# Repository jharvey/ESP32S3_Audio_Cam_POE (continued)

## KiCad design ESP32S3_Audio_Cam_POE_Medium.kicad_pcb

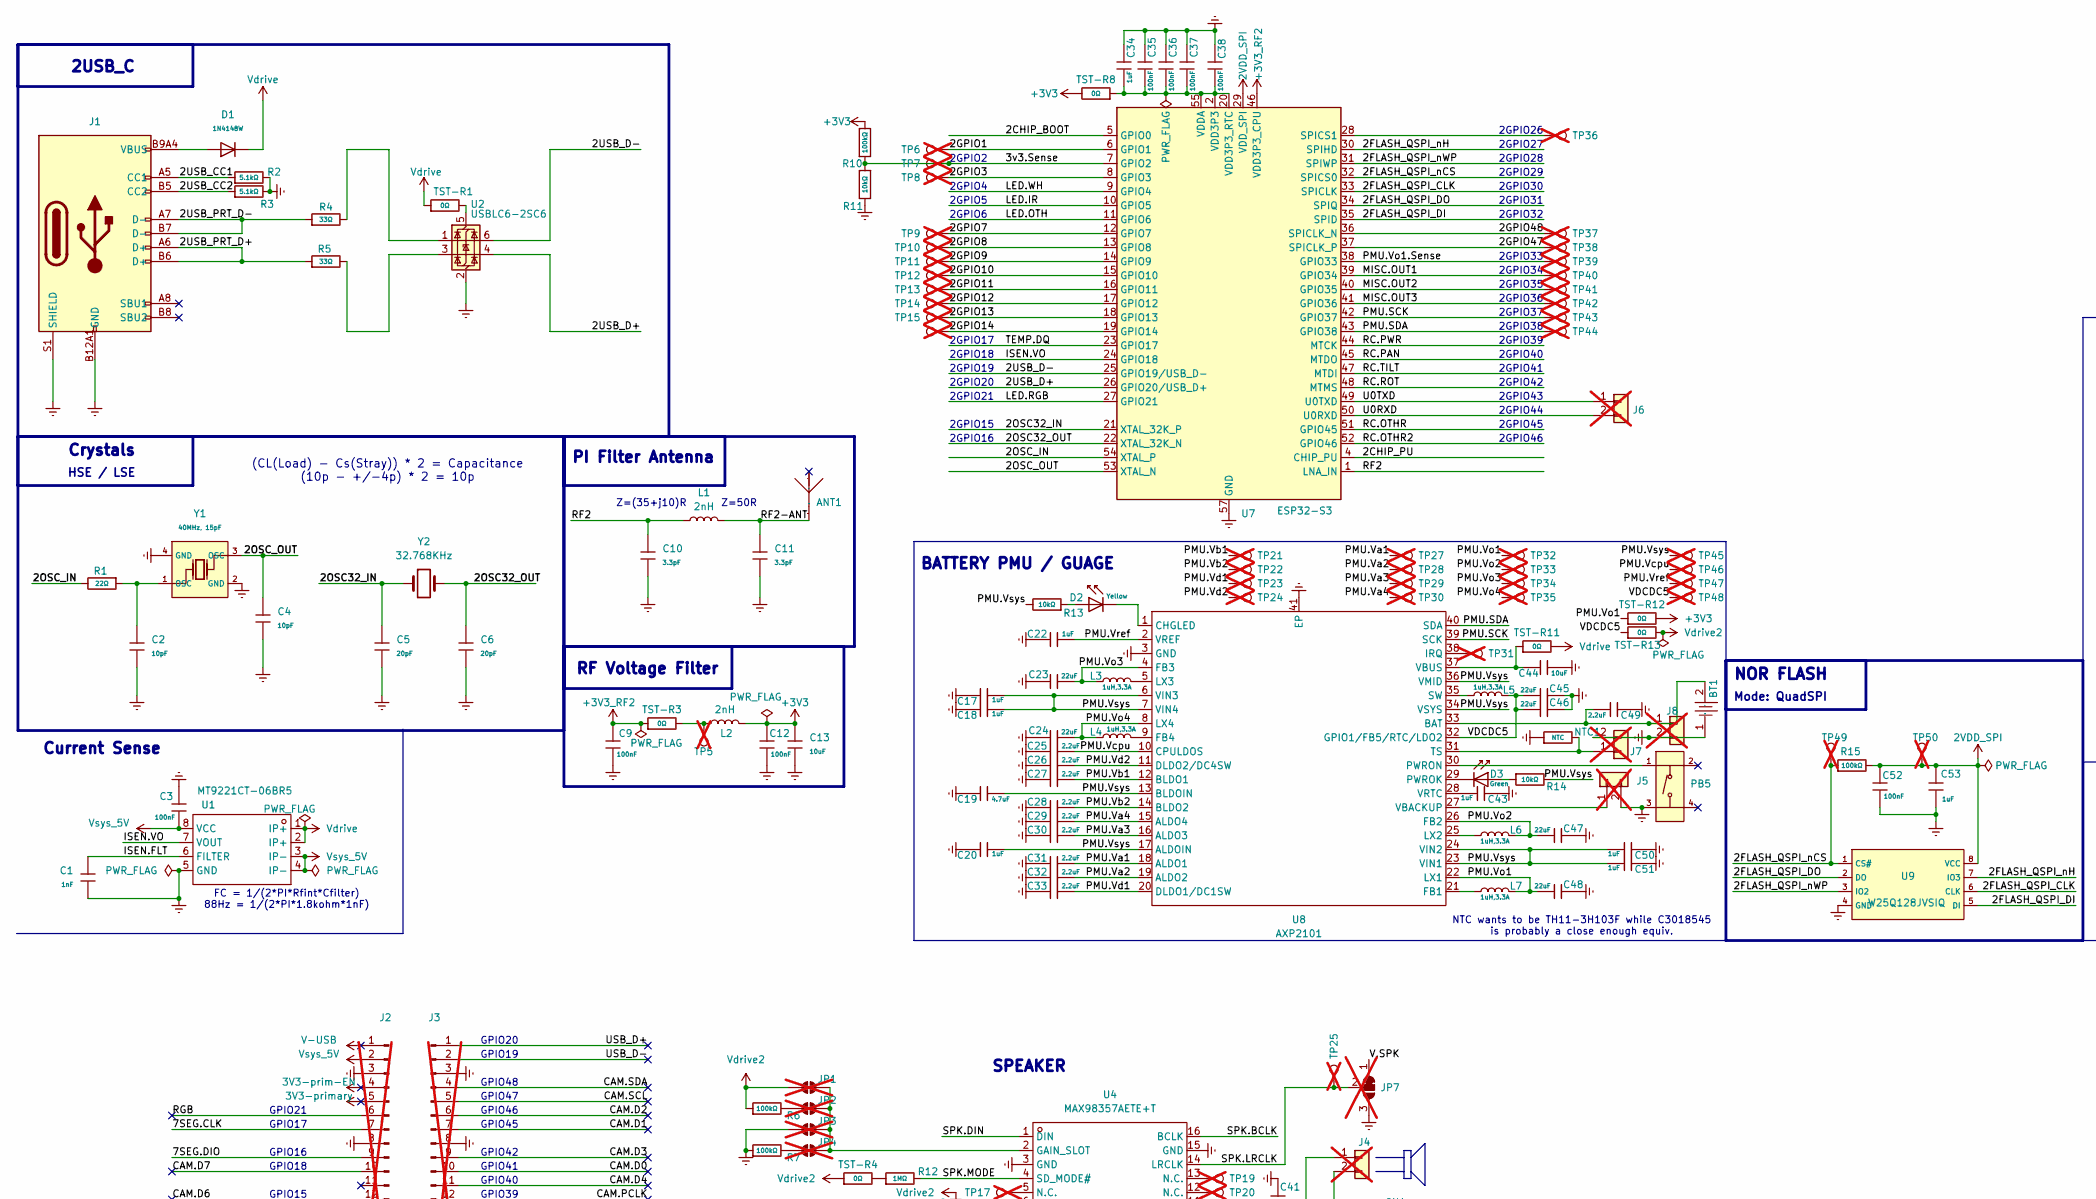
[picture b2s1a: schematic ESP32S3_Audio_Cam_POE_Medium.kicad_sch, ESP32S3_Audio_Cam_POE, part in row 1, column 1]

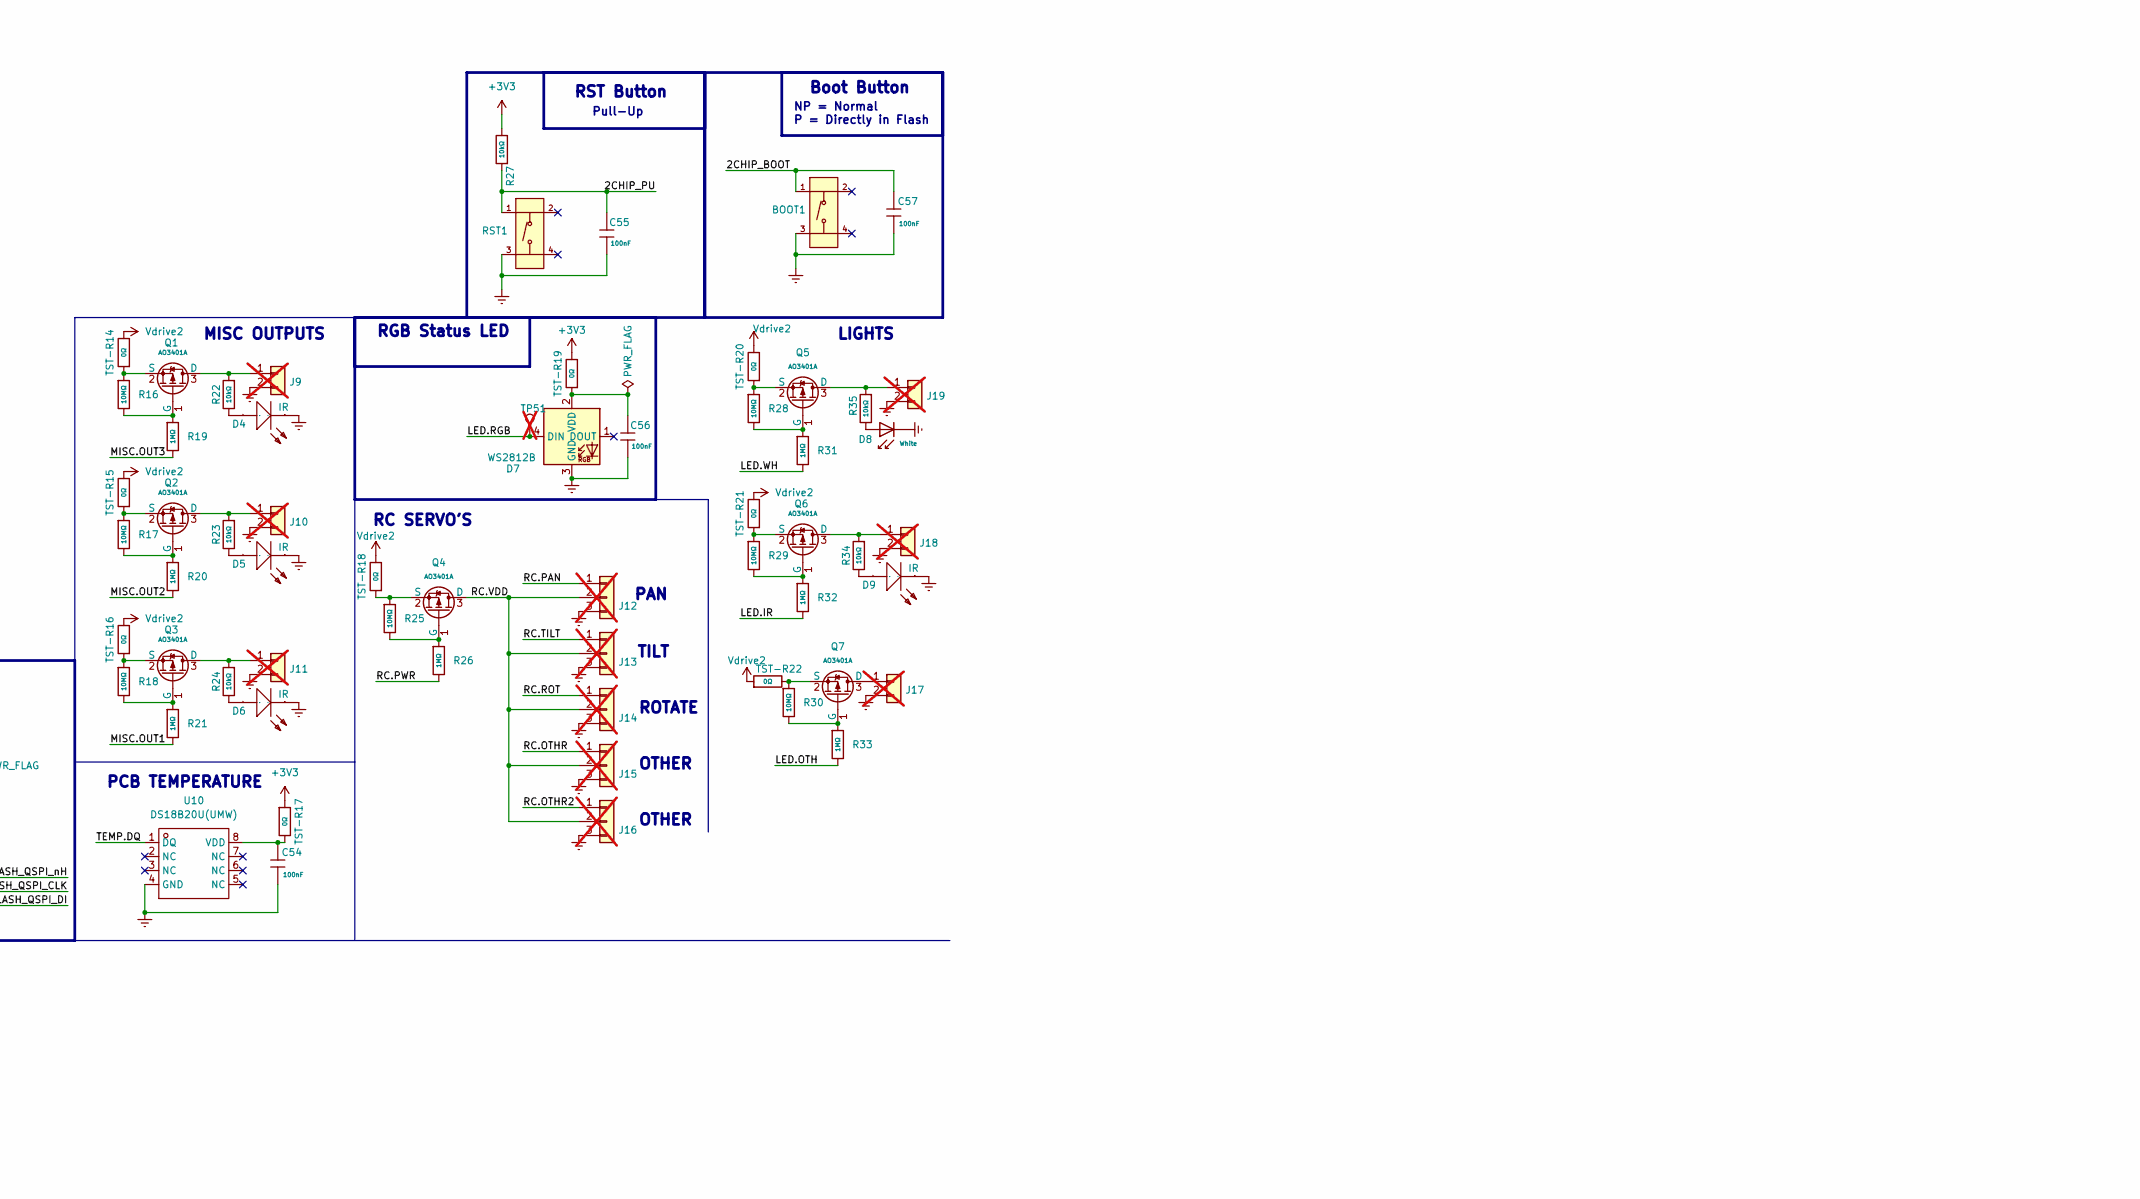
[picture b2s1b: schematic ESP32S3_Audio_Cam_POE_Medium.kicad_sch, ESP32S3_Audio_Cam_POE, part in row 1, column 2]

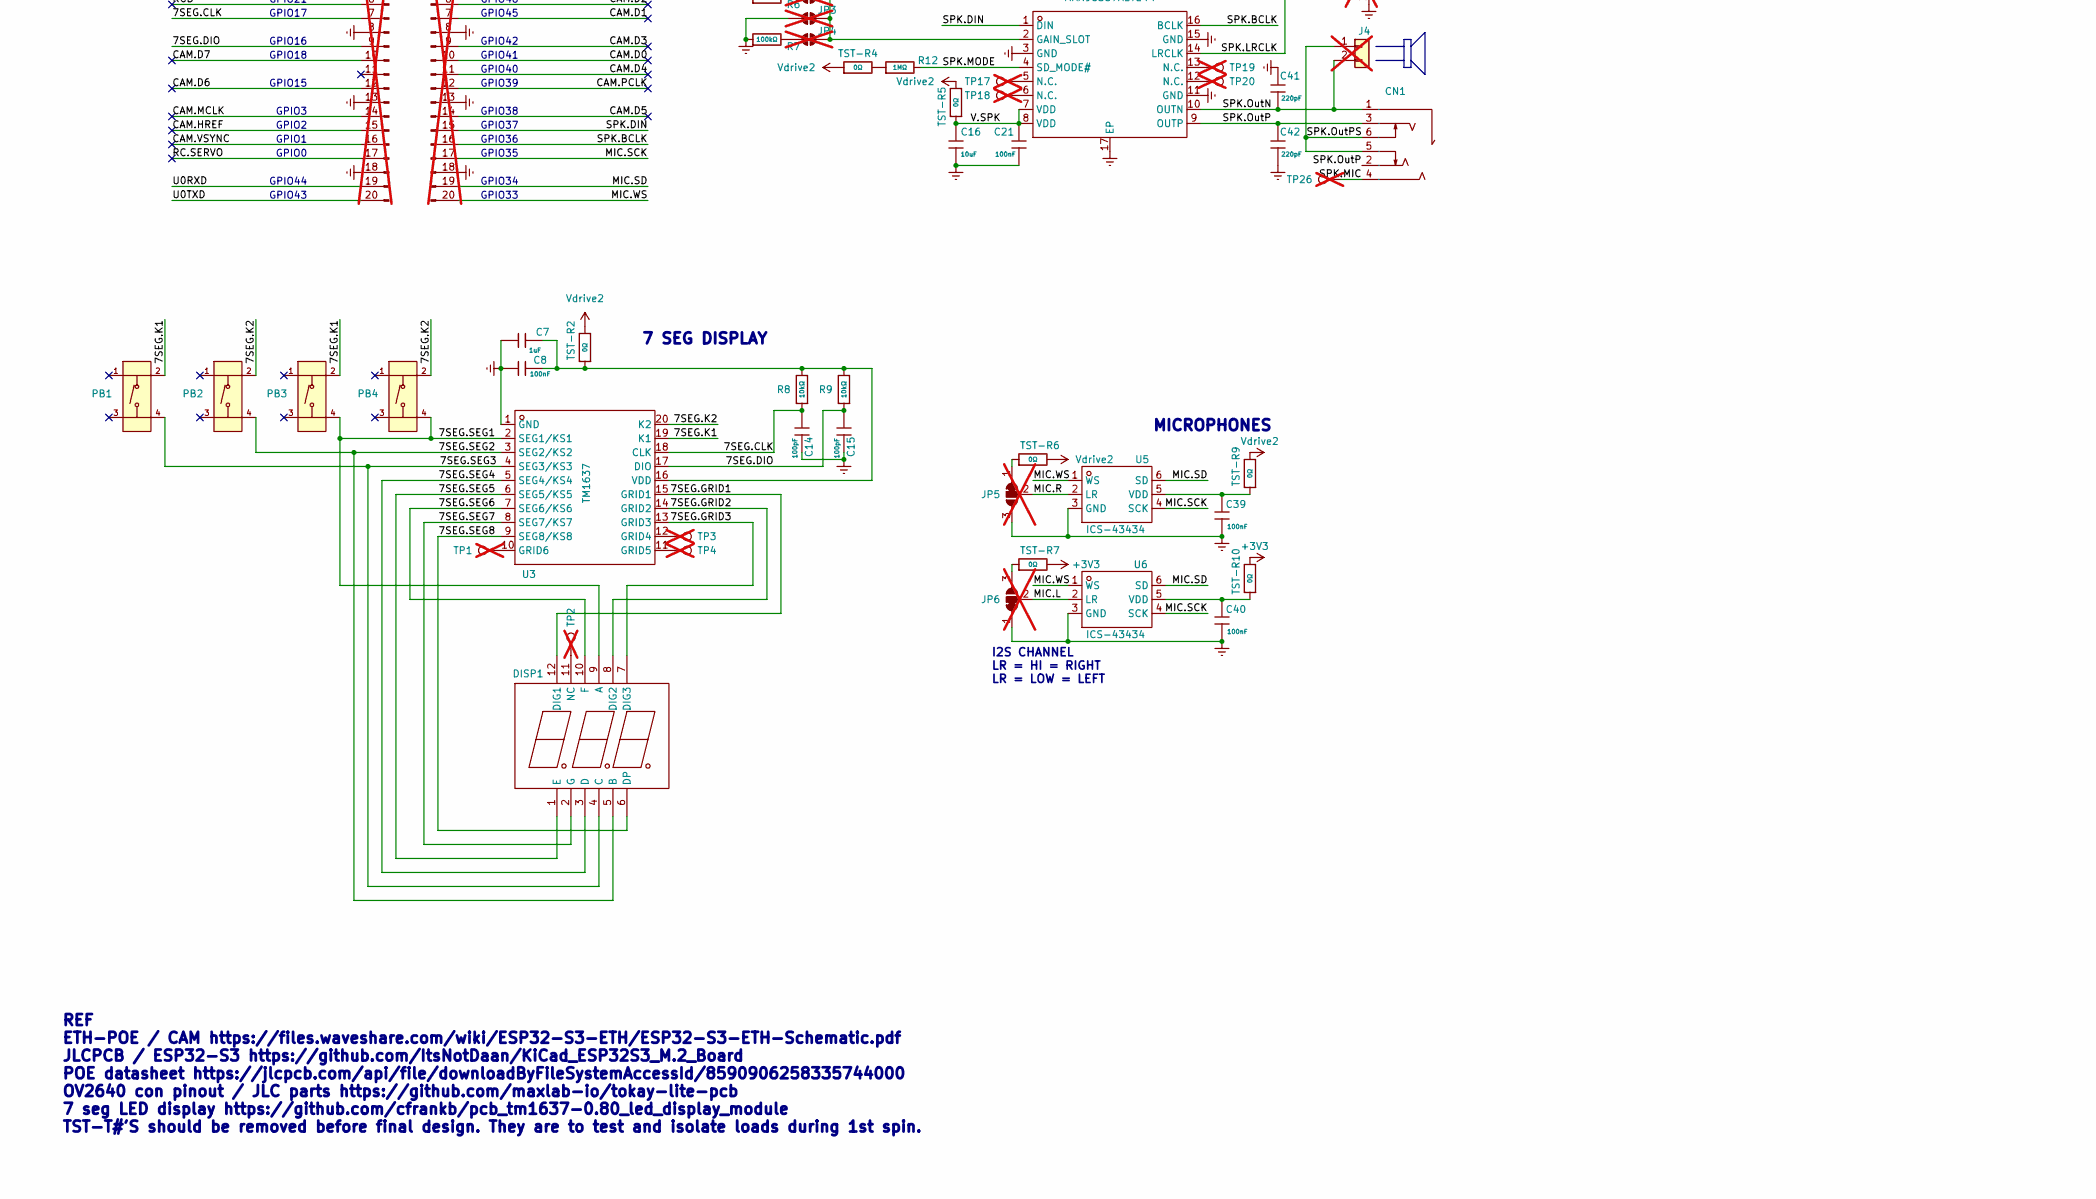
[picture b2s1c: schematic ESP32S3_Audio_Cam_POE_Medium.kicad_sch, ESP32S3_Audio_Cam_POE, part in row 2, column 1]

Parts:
ANT1: KH-3216-H0209; ANT-SMD_L3.2-W1.6-KH-3216F245C04; Manufacturer_Part_Number KH-3216-H0209; LCSC PART # C2925417
BOOT1: Tactile Button, 160gf; SW-SMD_4P-L5.1-W5.1-P3.70-LS6.5-TL-2; Voltage Rating (Dc) 12V; Part TS-1187A-B-A-B; LCSC C318884
BT1: BH-18650-B1BA002; BATTERY-SMD_18650-1S-L77.1-W20.7-1; Manufacturer Part BH-18650-B1BA002; LCSC C2988620
C1: 1nF; C_0402; Voltage Rated 50V; Tolerance ±10%; Part 0402B102K500NT; LCSC C1523
C2, C4: 10pF; C_0402; Voltage Rated 50V; Tolerance ±5%; Part CL05C100JB5NNNC; LCSC C32949
C3, C8, C9, C12, C21, C35, C36, C37, C38, C39, C40, C52, C54, C55, C56, C57: 100nF; C_0603; Voltage Rated 50V; Tolerance ±10%; Part CC0603KRX7R9BB104; LCSC C14663
C5, C6: 20pF; C_0402; Voltage Rated 50V; Tolerance ±5%; Part 0402CG200J500NT; LCSC C1554
C7, C34, C53: 1uF; C_0603; Voltage Rated 50V; Tolerance ±10%; Part CL10A105KB8NNNC; LCSC C15849
C10, C11: 3.3pF; C_0402; Voltage Rated 50V; Part 0402CG3R3C500NT; LCSC C1565
C13, C44: 10uF; C_0402; Voltage Rated 6.3V; Tolerance ±20%; Part CL05A106MQ5NUNC; LCSC C15525
C14, C15: 100pF; C_0402; Voltage Rated 50V; Tolerance ±5%; Part 0402CG101J500NT; LCSC C1546
C16: 10uF; C_0805; Voltage Rated 50V; Tolerance ±10%; Part GRM21BR61H106KE43L; LCSC C440198
C17, C18, C20, C22, C43, C50, C51: 1uF; C_0402; Voltage Rated 25V; Tolerance ±10%; Part CL05A105KA5NQNC; LCSC C52923
C19: 4.7uF; C_0402; Voltage Rated 10V; Tolerance ±20%; Part CL05A475MP5NRNC; LCSC C23733
C23, C24, C45, C46, C47, C48: 22uF; C_0603; Voltage Rated 6.3V; Tolerance ±20%; Part CL10A226MQ8NRNC; LCSC C59461
C25, C26, C27, C28, C29, C30, C31, C32, C33, C49: 2.2uF; C_0402; Voltage Rated 6.3V; Tolerance ±20%; Part CL05A225MQ5NSNC; LCSC C12530
C41, C42: 220pF; C_0402; Voltage Rated 50V; Tolerance ±10%; Part 0402B221K500NT; LCSC C1530
CN1: PJ-316C-6A; SMD_3.5mm_Audio_Connectors_(Headphones)_C707223; Manufacturer Part PJ-316C-6A; LCSC C707223
D1: 1N4148W; D_SOD-123; Forward Voltage (Vf@If) 1V@50mA; Reverse Voltage (Vr) 75V; Part 1N4148W; LCSC C81598
D2: Yellow; D_0805; Part KT-0805Y; LCSC C2296
D3: Green; D_0805; Part KT-0805G; LCSC C2297
D4, D5, D6, D9: IR; IR-LED_C131280; LCSC C131280
D7: WS2812B; LED-SMD_4P-L1.6-W1.5_XL-1615RGBC-WS2812B; LCSC C5349954
D8: White; D_0603; Part KT-0603W; LCSC C2290
DISP1: SLS0563DRA1GD; 3x7-seg_LED-RED_C2913084; LCSC C2913084
J1: Connector, USB-TYPE-C-16P; TYPE-C-SMD_HX-TYPE-C-16PIN; LCSC C2927039
J2, J3: Conn_01x20_Pin; PinHeader_1x20_P2.54mm_Vertical; not fitted
J4, J5, J6, J7, J8, J9, J10, J11, J17, J18, J19: Conn_01x02; PinHeader_1x02_P1.00mm_Vertical; not fitted
J12, J13, J14, J15, J16: Conn_01x03; PinHeader_1x03_P2.54mm_Vertical; not fitted
JP1, JP2, JP3, JP4: SolderJumper_2_Open; SolderJumper-2_P1.3mm_Open_TrianglePad1.0x1.5mm; not fitted
JP5, JP6, JP7: SolderJumper_3_Bridged12; SolderJumper-3_P1.3mm_Bridged12_Pad1.0x1.5mm; not fitted
L1, L2: 2nH; L_0603_1608Metric_Pad1.05x0.95mm_HandSolder; LCSC PART # C29682
L3, L4, L5, L6, L7: 1uH,3.3A; L_1008_2520Metric; Tolerance ±10%; Part SDFL2012Q1R0KTF; LCSC C435392
NTC1: NTC; R_0402; Overload Voltage (Max) 50V; Tolerance ±1%; Part 0402WGF1002TCE; LCSC C3018545
PB1, PB2, PB3, PB4, PB5: Tactile Button, 160gf; SW-SMD_4P-L5.1-W5.1-P3.70-LS6.5-TL-2; Voltage Rating (Dc) 12V; Part TS-1187A-B-A-B; LCSC C318884
Q1, Q2, Q3, Q4, Q5, Q6, Q7: AO3401A; Q_SOT-23; Part AO3401A; LCSC C15127
R1: 22Ω; R_0402; Overload Voltage (Max) 50V; Tolerance ±1%; Part 0402WGF220JTCE; LCSC C25092
R2, R3: 5.1kΩ; R_0402; Overload Voltage (Max) 50V; Tolerance ±1%; Part 0402WGF5101TCE; LCSC C25905
R4, R5: 33Ω; R_0402; Overload Voltage (Max) 50V; Tolerance ±1%; Part 0402WGF330JTCE; LCSC C25105
R6, R7: 100kΩ; R_0805; Overload Voltage (Max) 150V; Tolerance ±1%; Part 0805W8F1003T5E; LCSC C149504
R8, R9, R11, R13, R14, R22, R23, R24, R27, R34, R35: 10kΩ; R_0402; Overload Voltage (Max) 50V; Tolerance ±1%; Part 0402WGF1002TCE; LCSC C25744
R10, R15: 100kΩ; R_0402; Overload Voltage (Max) 50V; Tolerance ±1%; Part 0402WGF1003TCE; LCSC C25741
R12, R19, R20, R21, R26, R31, R32, R33: 1MΩ; R_0402; Overload Voltage (Max) 50V; Tolerance ±1%; Part 0402WGF1004TCE; LCSC C26083
R16, R17, R18, R25, R28, R29, R30: 10MΩ; R_0402; Overload Voltage (Max) 50V; Tolerance ±1%; Part 0402WGF1005TCE; LCSC C26082
RST1: Tactile Button, 160gf; SW-SMD_4P-L5.1-W5.1-P3.70-LS6.5-TL-2; Voltage Rating (Dc) 12V; Part TS-1187A-B-A-B; LCSC C318884
TP1, TP2, TP3, TP4, TP5, TP6, TP7, TP8, TP9, TP10, TP11, TP12, TP13, TP14, TP15, TP16, TP17, TP18, TP19, TP20, TP26, TP31, TP36, TP37, TP38, TP39, TP40, TP41, TP42, TP43, TP44, TP49, TP50, TP51: TestPoint; TestPoint_Pad_D1.0mm; not fitted
TP21, TP22, TP23, TP24, TP25, TP27, TP28, TP29, TP30, TP32, TP33, TP34, TP35, TP45, TP46, TP47, TP48: TestPoint; PinHeader_1x01_P1.00mm_Vertical; not fitted
TST-R1, TST-R2, TST-R3, TST-R4, TST-R5, TST-R6, TST-R7, TST-R8, TST-R9, TST-R10, TST-R11, TST-R12, TST-R13, TST-R14, TST-R15, TST-R16, TST-R17, TST-R18, TST-R19, TST-R20, TST-R21, TST-R22: 0Ω; R_0603; Overload Voltage (Max) 75V; Tolerance ±1%; Part 0603WAF0000T5E; LCSC C21189
U1: MT9221CT-06BR5; Current-sensor_MT9221CT-06BR5_C879632; LCSC C879632
U2: USBLC6-2SC6; SOT-23-6; Manufacturer_Part_Number USBLC6-2SC6; LCSC PART # C2827654
U3: TM1637; digital tube drivers_c2962580; LCSC C2962580
U4: MAX98357AETE+T; MAX98357AETE+T_C910544; Manufacturer Part MAX98357AETE+T
U5, U6: ICS-43434; ICS-43434_C5656610; LCSC C5656610
U7: ESP32-S3; QFN-56-1EP_7x7mm_P0.4mm_EP4x4mm_ThermalVias; LCSC C2913194
U8: AXP2101; QFN-40-1EP_5x5mm_P0.4mm_EP3.6x3.6mm_ThermalVias; LCSC C3036461
U9: W25Q128JVSIQ; SOIC-8_L5.3-W5.3-P1.27-LS8.0-BL; Part W25Q128JVSIQ; LCSC PART # C97521
U10: DS18B20U(UMW); DS18B20_C695836; LCSC C695836
Y1: 40MHz, 15pF; OSC-SMD_4P-L3.2-W2.5-BL_SIT8008BI; PartID X322540MPB4SI; LCSC C9010
Y2: 32.768KHz; Crystal_SMD_3215-2Pin_3.2x1.5mm; Manufacturer_Part_Number DST310S 32.768KHz; LCSC PART # C97604

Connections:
2VDD_SPI: C52.2, C53.1, R15.2, TP50.1, U7.29 (VDD_SPI), U9.8 (VCC)
3V3-prim-EN: J2.4
3V3-primary: J2.5
+3V3: C12.2, C13.1, L2.2, R10.2, R27.2, TST-R7.2, TST-R8.2, TST-R10.2, TST-R12.2, TST-R17.1, TST-R19.2
+3V3_RF2: C9.2, TST-R3.1, U7.46 (VDD3P3_CPU)
/2CHIP_BOOT: BOOT1.1 (A), C57.2, U7.5 (GPIO0)
/2CHIP_PU: C55.2, R27.1, RST1.1 (A), U7.4 (CHIP_PU)
/2FLASH_QSPI_CLK: U7.33 (SPICLK), U9.6 (CLK)
/2FLASH_QSPI_DI: U7.35 (SPID), U9.5 (DI)
/2FLASH_QSPI_DO: U7.34 (SPIQ), U9.2 (DO)
/2FLASH_QSPI_nCS: R15.1, TP49.1, U7.32 (SPICS0), U9.1 (CS#)
/2FLASH_QSPI_nH: U7.30 (SPIHD), U9.7 (IO3)
/2FLASH_QSPI_nWP: U7.31 (SPIWP), U9.3 (IO2)
/2GPIO1: TP6.1, U7.6 (GPIO1)
/2GPIO3: TP8.1, U7.8 (GPIO3)
/2GPIO7: TP9.1, U7.12 (GPIO7)
/2GPIO8: TP10.1, U7.13 (GPIO8)
/2GPIO9: TP11.1, U7.14 (GPIO9)
/2GPIO10: TP12.1, U7.15 (GPIO10)
/2GPIO11: TP13.1, U7.16 (GPIO11)
/2GPIO12: TP14.1, U7.17 (GPIO12)
/2GPIO13: TP15.1, U7.18 (GPIO13)
/2GPIO14: TP16.1, U7.19 (GPIO14)
/2GPIO47: TP38.1, U7.37 (SPICLK_P)
/2GPIO48: TP37.1, U7.36 (SPICLK_N)
/2OSC32_IN: C5.1, U7.21 (XTAL_32K_P), Y2.1
/2OSC32_OUT: C6.1, U7.22 (XTAL_32K_N), Y2.2
/2OSC_IN: R1.2, U7.54 (XTAL_P)
/2OSC_OUT: C4.1, U7.53 (XTAL_N), Y1.3 (OSC)
/2USB_CC1: J1.A5 (CC1), R2.1
/2USB_CC2: J1.B5 (CC2), R3.1
/2USB_D+: U2.4 (I/O2), U7.26 (GPIO20/USB_D+)
/2USB_D-: U2.6 (I/O1), U7.25 (GPIO19/USB_D-)
/2USB_PRT_D+: J1.A6 (D+), J1.B6 (D+), R5.1
/2USB_PRT_D-: J1.A7 (D-), J1.B7 (D-), R4.1
/3v3.Sense: R10.1, R11.1, TP7.1, U7.7 (GPIO2)
/7SEG.CLK: C14.2, J2.7, R8.1, U3.18 (CLK)
/7SEG.DIO: C15.2, J2.9, R9.1, U3.17 (DIO)
/7SEG.GRID1: DISP1.12 (DIG1), U3.15 (GRID1)
/7SEG.GRID2: DISP1.8 (DIG2), U3.14 (GRID2)
/7SEG.GRID3: DISP1.7 (DIG3), U3.13 (GRID3)
/7SEG.K1: PB1.2 (B), PB3.2 (B), U3.19 (K1)
/7SEG.K2: PB2.2 (B), PB4.2 (B), U3.20 (K2)
/7SEG.SEG1: DISP1.9 (A), PB3.4 (D), PB4.4 (D), U3.2 (SEG1/KS1)
/7SEG.SEG2: DISP1.5 (B), PB2.4 (D), U3.3 (SEG2/KS2)
/7SEG.SEG3: DISP1.4 (C), PB1.4 (D), U3.4 (SEG3/KS3)
/7SEG.SEG4: DISP1.3 (D), U3.5 (SEG4/KS4)
/7SEG.SEG5: DISP1.1 (E), U3.6 (SEG5/KS5)
/7SEG.SEG6: DISP1.10 (F), U3.7 (SEG6/KS6)
/7SEG.SEG7: DISP1.2 (G), U3.8 (SEG7/KS7)
/7SEG.SEG8: DISP1.6 (DP), U3.9 (SEG8/KS8)
/CAM.D0: J3.10
/CAM.D1: J3.7
/CAM.D2: J3.6
/CAM.D3: J3.9
/CAM.D4: J3.11
/CAM.D5: J3.14
/CAM.D6: J2.12
/CAM.D7: J2.10
/CAM.HREF: J2.15
/CAM.MCLK: J2.14
/CAM.PCLK: J3.12
/CAM.SCL: J3.5
/CAM.SDA: J3.4
/CAM.VSYNC: J2.16
/ISEN.FLT: C1.1, U1.6 (FILTER)
/ISEN.VO: U1.7 (VOUT), U7.24 (GPIO18)
/LED.IR: R32.2, U7.10 (GPIO5)
/LED.OTH: R33.2, U7.11 (GPIO6)
/LED.RGB: D7.4 (DIN), TP51.1, U7.27 (GPIO21)
/LED.WH: R31.2, U7.9 (GPIO4)
/MIC.L: JP6.2 (C), U6.2 (LR)
/MIC.R: JP5.2 (C), U5.2 (LR)
/MIC.SCK: J3.17, U5.4 (SCK), U6.4 (SCK)
/MIC.SD: J3.19, U5.6 (SD), U6.6 (SD)
/MIC.WS: J3.20, U5.1 (WS), U6.1 (WS)
/MISC.OUT1: R21.2, TP40.1, U7.39 (GPIO34)
/MISC.OUT2: R20.2, TP41.1, U7.40 (GPIO35)
/MISC.OUT3: R19.2, TP42.1, U7.41 (GPIO36)
/PMU.SCK: TP43.1, U7.42 (GPIO37), U8.39 (SCK)
/PMU.SDA: TP44.1, U7.43 (GPIO38), U8.40 (SDA)
/PMU.Va1: C31.2, TP27.1, U8.18 (ALDO1)
/PMU.Va2: C32.2, TP28.1, U8.19 (ALDO2)
/PMU.Va3: C30.2, TP29.1, U8.16 (ALDO3)
/PMU.Va4: C29.2, TP30.1, U8.15 (ALDO4)
/PMU.Vb1: C27.2, TP21.1, U8.12 (BLDO1)
/PMU.Vb2: C28.2, TP22.1, U8.14 (BLDO2)
/PMU.Vcpu: C25.2, TP46.1, U8.10 (CPULDOS)
/PMU.Vd1: C33.2, TP23.1, U8.20 (DLDO1/DC1SW)
/PMU.Vd2: C26.2, TP24.1, U8.11 (DLDO2/DC4SW)
/PMU.Vo1: C48.2, L7.1, TP32.1, TST-R12.1, U8.22 (LX1)
/PMU.Vo1.Sense: TP39.1, U7.38 (GPIO33)
/PMU.Vo2: C47.2, L6.1, TP33.1, U8.26 (FB2)
/PMU.Vo3: C23.2, L3.1, TP34.1, U8.4 (FB3)
/PMU.Vo4: C24.2, L4.1, TP35.1, U8.8 (LX4)
/PMU.Vref: C22.2, TP47.1, U8.2 (VREF)
/PMU.Vsys: C17.2, C18.2, C19.2, C20.2, C50.2, C51.2, R13.2, R14.2, TP45.1, U8.6 (VIN3), U8.7 (VIN4), U8.13 (BLDOIN), U8.17 (ALDOIN), U8.23 (VIN1), U8.24 (VIN2), U8.34 (VSYS), U8.36 (VMID)
/RC.OTHR: J15.1, U7.51 (GPIO45)
/RC.OTHR2: J16.1, U7.52 (GPIO46)
/RC.PAN: J12.1, U7.45 (MTDO)
/RC.PWR: R26.2, U7.44 (MTCK)
/RC.ROT: J14.1, U7.48 (MTMS)
/RC.SERVO: J2.17
/RC.TILT: J13.1, U7.47 (MTDI)
/RC.VDD: J12.2, J13.2, J14.2, J15.2, J16.2, Q4.3 (D)
/RF2: C10.1, L1.1, U7.1 (LNA_IN)
/RF2-ANT: ANT1.1 (ANT), C11.1, L1.2
/RGB: J2.6
/SPK.BCLK: J3.16, U4.16 (BCLK)
/SPK.DIN: J3.15, U4.1 (DIN)
/SPK.LRCLK: JP7.2 (C), TP25.1, U4.14 (LRCLK)
/SPK.MIC: CN1.4, TP26.1
/SPK.MODE: R12.2, U4.4 (SD_MODE#)
/SPK.OutN: C41.2, CN1.1, J4.2, U4.10 (OUTN)
/SPK.OutP: C42.1, CN1.2, CN1.3, U4.9 (OUTP)
/SPK.OutPS: CN1.5, CN1.6, J4.1
/TEMP.DQ: U7.23 (GPIO17), U10.1 (DQ)
/U0RXD: J2.19, J6.2, U7.50 (U0RXD)
/U0TXD: J2.20, J6.1, U7.49 (U0TXD)
/USB_D+: J3.1
/USB_D-: J3.2
/V.SPK: C16.1, C21.1, JP7.1 (A), TST-R5.1, U4.7 (VDD), U4.8 (VDD)
/VDCDC5: C45.2, C46.2, L5.1, TP48.1, TST-R13.1, U8.32 (GPIO1/FB5/RTC/LDO2)
COM: BOOT1.3 (C), BT1.1, C1.2, C2.2, C3.2, C4.2, C5.2, C6.2, C7.1, C8.2, C9.1, C10.2, C11.2, C12.1, C13.2, C14.1, C15.1, C16.2, C17.1, C18.1, C19.1, C20.1, C21.2, C22.1, C23.1, C24.1, C25.1, C26.1, C27.1, C28.1, C29.1, C30.1, C31.1, C32.1, C33.1, C34.1, C35.2, C36.2, C37.2, C38.2, C39.1, C40.1, C41.1, C42.2, C43.1, C44.2, C45.1, C46.1, C47.1, C48.1, C49.1, C50.1, C51.1, C52.1, C53.2, C54.1, C55.1, C56.1, C57.1, D4.1 (C), D5.1 (C), D6.1 (C), D7.3 (GND), D8.1, D9.1 (C), J1.A12B1 (GND), J1.B12A1 (GND), J1.S1 (SHIELD), J2.3, J2.8, J2.13, J2.18, J3.3, J3.8, J3.13, J3.18, J5.2, J7.2, J8.2, J9.2, J10.2, J11.2, J12.3, J13.3, J14.3, J15.3, J16.3, J17.2, J18.2, J19.2, JP3.1 (A), JP5.3 (B), JP6.1 (A), JP7.3 (B), NTC1.1, PB5.3 (C), R2.2, R3.2, R7.1, R11.2, RST1.3 (C), U1.5 (GND), U2.2 (GND), U3.1 (GND), U4.3 (GND), U4.11 (GND), U4.15 (GND), U4.17 (EP), U5.3 (GND), U6.3 (GND), U7.57 (GND), U8.3 (GND), U8.41 (EP), U9.4 (GND), U10.4 (GND), Y1.2 (GND), Y1.4 (GND)
unnamed: C2.1, R1.1, Y1.1 (OSC)
unnamed: D1.2, J1.A9B4 (VBUS), J1.B9A4 (VBUS)
unnamed: D2.2, R13.1
unnamed: D3.2, R14.1
unnamed: D4.2 (A), R22.2
unnamed: D5.2 (A), R23.2
unnamed: D6.2 (A), R24.2
unnamed: C56.2, D7.2 (VDD), TST-R19.1
unnamed: D8.2, R35.2
unnamed: D9.2 (A), R34.2
unnamed: DISP1.11 (NC), TP2.1
unnamed: J5.1, U8.27 (VBACKUP)
unnamed: J7.1, NTC1.2, U8.31 (TS)
unnamed: BT1.2, C49.2, J8.1, U8.33 (BAT)
unnamed: J9.1, Q1.3 (D), R22.1
unnamed: J10.1, Q2.3 (D), R23.1
unnamed: J11.1, Q3.3 (D), R24.1
unnamed: J17.1, Q7.3 (D)
unnamed: J18.1, Q6.3 (D), R34.1
unnamed: J19.1, Q5.3 (D), R35.1
unnamed: JP1.2 (B), JP2.2 (B), JP3.2 (B), JP4.2 (B), U4.2 (GAIN_SLOT)
unnamed: JP2.1 (A), R6.2
unnamed: JP4.1 (A), R7.2
unnamed: JP5.1 (A), TST-R6.1
unnamed: JP6.3 (B), TST-R7.1
unnamed: L2.1, TP5.1, TST-R3.2
unnamed: PB5.1 (A), U8.30 (PWRON)
unnamed: Q1.1 (G), R16.2, R19.1
unnamed: Q1.2 (S), R16.1, TST-R14.1
unnamed: Q2.1 (G), R17.2, R20.1
unnamed: Q2.2 (S), R17.1, TST-R15.1
unnamed: Q3.1 (G), R18.2, R21.1
unnamed: Q3.2 (S), R18.1, TST-R16.1
unnamed: Q4.1 (G), R25.2, R26.1
unnamed: Q4.2 (S), R25.1, TST-R18.1
unnamed: Q5.1 (G), R28.2, R31.1
unnamed: Q5.2 (S), R28.1, TST-R20.1
unnamed: Q6.1 (G), R29.2, R32.1
unnamed: Q6.2 (S), R29.1, TST-R21.1
unnamed: Q7.1 (G), R30.2, R33.1
unnamed: Q7.2 (S), R30.1, TST-R22.2
unnamed: R4.2, U2.1 (I/O1)
unnamed: R5.2, U2.3 (I/O2)
unnamed: R12.1, TST-R4.2
unnamed: TP17.1, U4.5 (N.C.)
unnamed: TP18.1, U4.6 (N.C.)
unnamed: TP19.1, U4.13 (N.C.)
unnamed: TP20.1, U4.12 (N.C.)
unnamed: TST-R1.2, U2.5 (VBUS)
unnamed: TP3.1, U3.12 (GRID4)
unnamed: TP4.1, U3.11 (GRID5)
unnamed: TP1.1, U3.10 (GRID6)
unnamed: C7.2, C8.1, R8.2, R9.2, TST-R2.1, U3.16 (VDD)
unnamed: C39.2, TST-R9.1, U5.5 (VDD)
unnamed: C40.2, TST-R10.1, U6.5 (VDD)
unnamed: TP36.1, U7.28 (SPICS1)
unnamed: C34.2, C35.1, C36.1, C37.1, C38.1, TST-R8.1, U7.2 (VDD3P3), U7.3 (VDD3P3), U7.20 (VDD3P3_RTC), U7.55 (VDDA), U7.56 (VDDA)
unnamed: D2.1, U8.1 (CHGLED)
unnamed: L7.2, U8.21 (FB1)
unnamed: L4.2, U8.9 (FB4)
unnamed: TP31.1, U8.38 (IRQ)
unnamed: L6.2, U8.25 (LX2)
unnamed: L3.2, U8.5 (LX3)
unnamed: D3.1, U8.29 (PWROK)
unnamed: L5.2, U8.35 (SW)
unnamed: C44.1, TST-R11.1, U8.37 (VBUS)
unnamed: C43.2, U8.28 (VRTC)
unnamed: C54.2, TST-R17.2, U10.8 (VDD)
V-USB: J2.1
Vdrive: D1.1, TST-R1.1, TST-R11.2, U1.1 (IP+), U1.2 (IP+)
Vdrive2: JP1.1 (A), R6.1, TST-R2.2, TST-R4.1, TST-R5.2, TST-R6.2, TST-R9.2, TST-R13.2, TST-R14.2, TST-R15.2, TST-R16.2, TST-R18.2, TST-R20.2, TST-R21.2, TST-R22.1
Vsys_5V: C3.1, J2.2, U1.3 (IP-), U1.4 (IP-), U1.8 (VCC)

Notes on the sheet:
GPIO15
GPIO37
RF Voltage Filter
GPIO0
2GPIO18
Current Sense
RST Button
expected risky area -- camera connector pinout, is pin1 really pin 1 not 24? -- I2S microphones and amplifier, should they be the same lines like code suggests -- I2C, does this need pull up, or can internal pullup suffice? -- POE ethernet, complete unknown. Fingers crossed. TODO -- make office con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
2GPIO21
Boot Button
LIGHTS
RC SERVO'S
BATTERY PMU / GUAGE
GPIO21
Crystals
2GPIO2
2GPIO28
2GPIO17
ROTATE
MICROPHONES
GPIO46
2GPIO26
NTC wants to be TH11-3H103F while C3018545 is probably a close enough equiv.
NOR FLASH
GPIO36
GPIO34
Z=50R
2GPIO41
2GPIO27
2GPIO29
I2S CHANNEL LR = HI = RIGHT LR = LOW = LEFT
GPIO1
Mode: QuadSPI
2GPIO36
Z=(35+j10)R
2GPIO30
2GPIO44
PI Filter Antenna
GPIO20
GPIO3

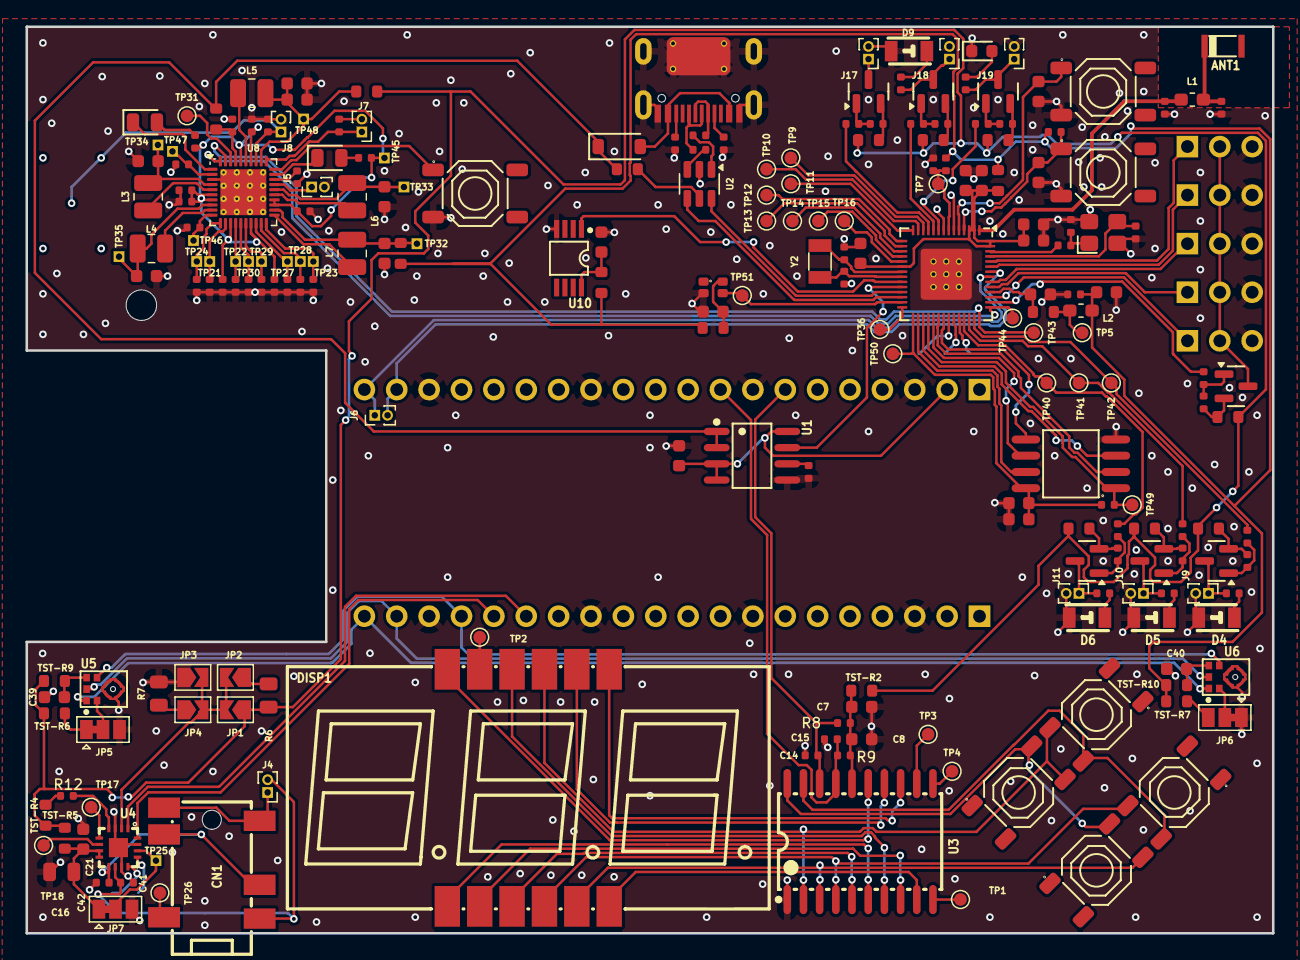
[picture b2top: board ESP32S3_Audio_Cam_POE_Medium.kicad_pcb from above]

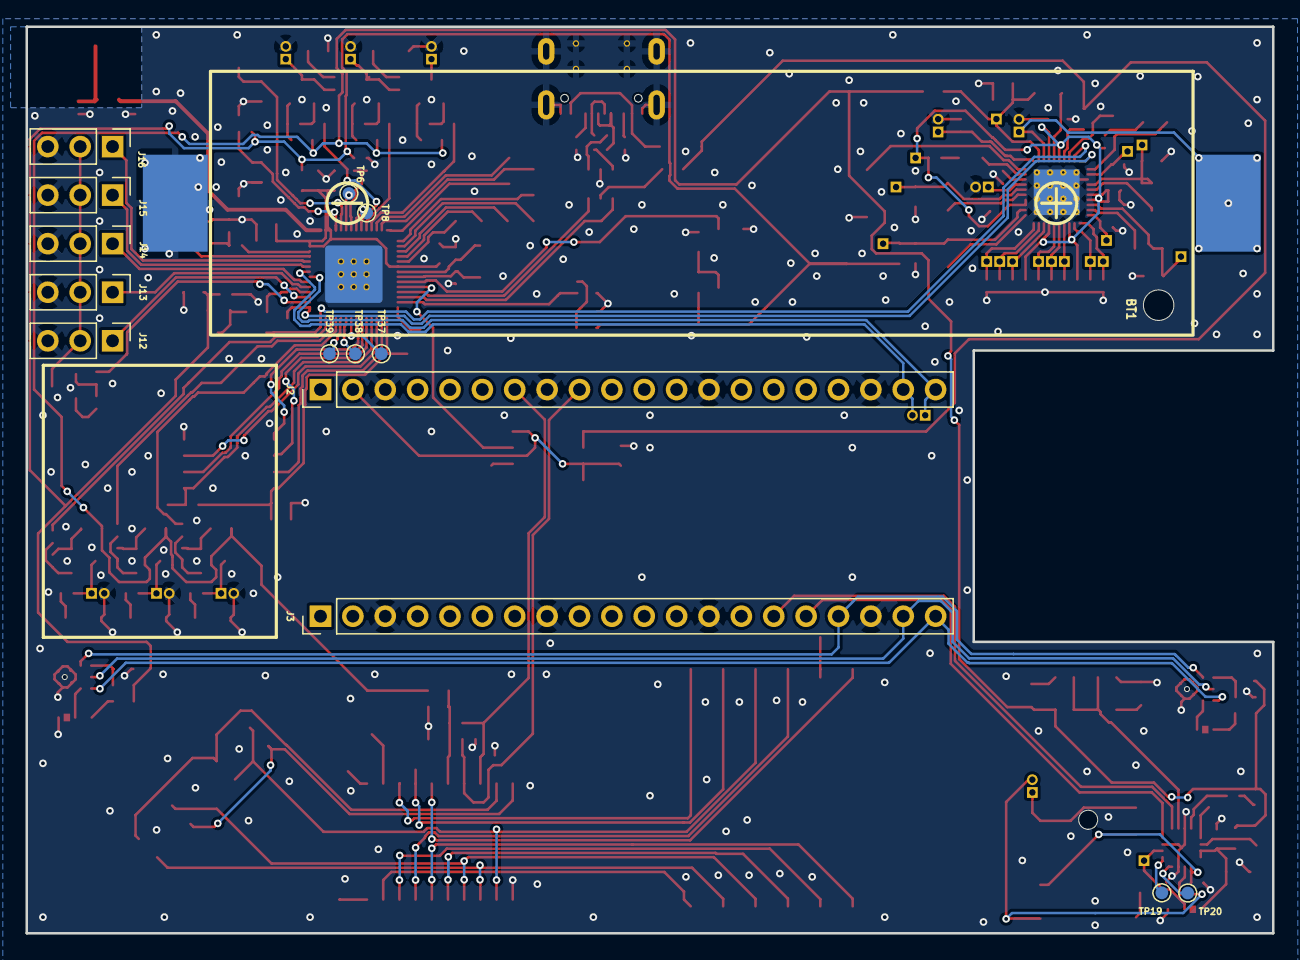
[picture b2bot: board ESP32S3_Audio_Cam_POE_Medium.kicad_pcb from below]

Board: 2 copper layers, 97.8 x 71.1 mm, 238 parts (15 on the bottom side), 175 nets.

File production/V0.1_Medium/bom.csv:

Designator,Footprint,Quantity,Value,LCSC Part #
ANT1,ANT-SMD_L3.2-W1.6-KH-3216F245C04,1,KH-3216-H0209,
"BOOT1, PB1, PB2, PB3, PB4, PB5, RST1",SW-SMD_4P-L5.1-W5.1-P3.70-LS6.5-TL-2,7,"Tactile Button, 160gf",C318884
BT1,BATTERY-SMD_18650-1S-L77.1-W20.7-1,1,BH-18650-B1BA002,C2988620
C1,C_0402,1,1nF,C1523
"C10, C11",C_0402,2,3.3pF,C1565
"C12, C21, C3, C35, C36, C37, C38, C39, C40, C52, C54, C55, C56, C57, C8, C9",C_0603,16,100nF,C14663
"C13, C44",C_0402,2,10uF,C15525
"C14, C15",C_0402,2,100pF,C1546
C16,C_0805,1,10uF,C440198
"C17, C18, C20, C22, C43, C50, C51",C_0402,7,1uF,C52923
C19,C_0402,1,4.7uF,C23733
"C2, C4",C_0402,2,10pF,C32949
"C23, C24, C45, C46, C47, C48",C_0603,6,22uF,C59461
"C25, C26, C27, C28, C29, C30, C31, C32, C33, C49",C_0402,10,2.2uF,C12530
"C34, C53, C7",C_0603,3,1uF,C15849
"C41, C42",C_0402,2,220pF,C1530
"C5, C6",C_0402,2,20pF,C1554
CN1,SMD_3.5mm_Audio_Connectors_(Headphones)_C707223,1,PJ-316C-6A,C707223
D1,D_SOD-123,1,1N4148W,C81598
D2,D_0805,1,Yellow,C2296
D3,D_0805,1,Green,C2297
"D4, D5, D6, D9",IR-LED_C131280,4,IR,C131280
D7,LED-SMD_4P-L1.6-W1.5_XL-1615RGBC-WS2812B,1,WS2812B,C5349954
D8,D_0603,1,White,C2290
DISP1,3x7-seg_LED-RED_C2913084,1,SLS0563DRA1GD,C2913084
J1,TYPE-C-SMD_HX-TYPE-C-16PIN,1,"Connector, USB-TYPE-C-16P",C2927039
"J10, J11, J17, J18, J19, J4, J5, J6, J7, J8, J9",PinHeader_1x02_P1.00mm_Vertical,11,Conn_01x02,
"J12, J13, J14, J15, J16",PinHeader_1x03_P2.54mm_Vertical,5,Conn_01x03,
"J2, J3",PinHeader_1x20_P2.54mm_Vertical,2,Conn_01x20_Pin,
"L1, L2",0603,2,2nH,
"L3, L4, L5, L6, L7",1008,5,"1uH,3.3A",C435392
NTC1,R_0402,1,NTC,C3018545 
"Q1, Q2, Q3, Q4, Q5, Q6, Q7",Q_SOT-23,7,AO3401A,C15127
R1,R_0402,1,22Ω,C25092
"R10, R15",R_0402,2,100kΩ,C25741
"R11, R13, R14, R22, R23, R24, R27, R34, R35, R8, R9",R_0402,11,10kΩ,C25744
"R12, R19, R20, R21, R26, R31, R32, R33",R_0402,8,1MΩ,C26083
"R16, R17, R18, R25, R28, R29, R30",R_0402,7,10MΩ,C26082
"R2, R3",R_0402,2,5.1kΩ,C25905
"R4, R5",R_0402,2,33Ω,C25105
"R6, R7",R_0805,2,100kΩ,C149504
"TP1, TP10, TP11, TP12, TP13, TP14, TP15, TP16, TP17, TP18, TP19, TP2, TP20, TP26, TP3, TP31, TP36, TP37, TP38, TP39, TP4, TP40, TP41, TP42, TP43, TP44, TP49, TP5, TP50, TP51, TP6, TP7, TP8, TP9",TestPoint_Pad_D1.0mm,34,TestPoint,
"TP21, TP22, TP23, TP24, TP25, TP27, TP28, TP29, TP30, TP32, TP33, TP34, TP35, TP45, TP46, TP47, TP48",PinHeader_1x01_P1.00mm_Vertical,17,TestPoint,
"TST-R1, TST-R10, TST-R11, TST-R12, TST-R13, TST-R14, TST-R15, TST-R16, TST-R17, TST-R18, TST-R19, TST-R2, TST-R20, TST-R21, TST-R22, TST-R3, TST-R4, TST-R5, TST-R6, TST-R7, TST-R8, TST-R9",R_0603,22,0Ω,C21189
U1,Current-sensor_MT9221CT-06BR5_C879632,1,MT9221CT-06BR5,C879632
U10,DS18B20_C695836,1,DS18B20U(UMW),C695836
U2,SOT-23-6,1,USBLC6-2SC6,
U3,digital tube drivers_c2962580,1,TM1637,C2962580
U4,MAX98357AETE+T_C910544,1,MAX98357AETE+T,
"U5, U6",ICS-43434_C5656610,2,ICS-43434,C5656610
U7,QFN-56-1EP_7x7mm_P0.4mm_EP4x4mm_ThermalVias,1,ESP32-S3,C2913194 
U8,QFN-40-1EP_5x5mm_P0.4mm_EP3.6x3.6mm_ThermalVias,1,AXP2101,C3036461
U9,SOIC-8_L5.3-W5.3-P1.27-LS8.0-BL,1,W25Q128JVSIQ,
Y1,OSC-SMD_4P-L3.2-W2.5-BL_SIT8008BI,1,"40MHz, 15pF",C9010
Y2,Crystal_SMD_3215-2Pin_3.2x1.5mm,1,32.768KHz,

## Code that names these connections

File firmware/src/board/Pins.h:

// ESP32-S3 (U7) pin map, taken from the schematic netlist after the 2026-11-22 pin remap
// (pins re-assigned to untangle the ratsnest for the single-sided layout), and the 2026-11-24 camera remap:
// the camera's fast lines (D0-D7, PCLK, XCLK) moved to U7's left and bottom edges, nearest the FPC, so they
// reach it on the top layer without crossing USB (pins 25/26). Then SD and Ethernet moved to the right edge
// (pins 6-11, GPIO1-6): their lines leave the bottom-right corner and pass under the camera bundle to the SD
// card and W5500 (lower left) without crossing it.
// Regenerate this if the schematic changes.
#pragma once

namespace pins {

constexpr int RGB_LED_GPIO = 0;  // D9 WS2812B data on GPIO0 via R110 33R (CHIP_BOOT strap: driven only after
                                 // boot; R109 10k pull-up holds it high at reset; C71 debounce cap not fitted)

// I2C bus: PCA9685 0x40 (U20), TCA9555 0x20 (U21), AXP2101 0x34 (U18)
constexpr int I2C_SCL = 43;
constexpr int I2C_SDA = 12;

// Shared SPI: W5500 Ethernet (U9) and RFM95 LoRa (U19)
constexpr int SPI_MOSI = 6;     // GPIO matrix
constexpr int SPI_MISO = 5;
constexpr int SPI_SCLK = 4;
constexpr int ETH_CS = 13;
constexpr int LORA_CS = 11;
constexpr int RADAR_RX = 10;  // /RADAR.TX: the mmWave people sensor's data line (J21 LD2410C or J22 LD2450), 256000 baud
// LoRa DIO0 (LORA_IRQ) moved to U22 P14, and the LD2410C's OUT pin is on U22 P13 (board/Panel.h): both are read through the expander

// PDM microphones U16/U17 (L/R by JP7/JP8) on I2S0
constexpr int MIC_CLK = 9;
constexpr int MIC_DATA = 7;

// Speaker amp MAX98357A (U15) on I2S1
constexpr int SPK_BCLK = 16;  // net /ESP.MIC.SCK (XTAL_32K_N, free: no 32 kHz crystal fitted)
constexpr int SPK_WS = 8;     // net /ESP.I2S.WS
constexpr int SPK_DOUT = 14;  // net /SPK.DIN

// SD card, SDMMC 1-bit (DAT3 pulled up by R29, not on a GPIO)
constexpr int SD_CLK = 2;
constexpr int SD_CMD = 3;    // net /SD.MOSI. GPIO3 is the JTAG-source strap, ignored unless its eFuse is burned
constexpr int SD_D0 = 1;

// Camera (OV2640 / OV5640). No PWDN/RESET GPIOs; power via TCA9555 P03.
constexpr int CAM_XCLK = 45;  // net /CAM.MCLK, U7 pin 51. Strapping pin, but only the ESP32 drives it
constexpr int CAM_SIOD = 15;  // CAM.SDA
constexpr int CAM_SIOC = 17;  // CAM.SCL
constexpr int CAM_VSYNC = 18;
constexpr int CAM_HREF = 21;
constexpr int CAM_PCLK = 41;  // U7 pin 47
constexpr int CAM_D0 = 39, CAM_D1 = 47, CAM_D2 = 48, CAM_D3 = 38;  // pins 44, 37 (SPICLK_P), 36 (SPICLK_N), 43
constexpr int CAM_D4 = 40, CAM_D5 = 42, CAM_D6 = 44, CAM_D7 = 46;  // pins 45, 48, 50 (U0RXD), 52 (strapping)
// GPIO45 (VDD_SPI voltage strap) carries XCLK, an ESP32 output: the camera can't hold it high at reset.
// GPIO46 carries D7, a camera output. GPIO46 only matters with GPIO0 low (download mode): GPIO0 = 0 and
// GPIO46 = 1 is not a valid boot mode. At power-up the camera is off (TCA9555 P04 is an input at reset, R14
// holds Q1 off), so this only bites if the camera is powered when BOOT is held. Keep it that way: power the camera off (CAM_PWR high) before
// any restart. Normal SPI boot (GPIO0 high) ignores GPIO46.
// GPIO3 (SD.MOSI = SD CMD) is the JTAG-source strap; it is ignored unless the STRAP_JTAG_SEL eFuse is burned.

// TCA9555 (U21) port bits
namespace exp {
constexpr int TM_CLK = 6;      // P06  TM1637 CLK (display + key scan)
constexpr int TM_DIO = 7;      // P07  TM1637 DIO
constexpr int PWM_OE = 0;      // P00  PCA9685 /OE, high = outputs LOW = every output switch off
constexpr int CAM_PWR = 4;     // P04  camera power (Q1 via R15)
constexpr int LORA_RST = 5;    // P05
constexpr int PMU_IRQ = 1;     // P01  AXP2101 IRQ, input
constexpr int ETH_INT = 3;     // P03  W5500 INT, input (W5500 runs polled)
constexpr int ETH_RST = 2;     // P02  W5500 reset (via R27)
// Port 1 (bits 8..15): the output switches' fault flags (SY6288 OCB, open-drain, low = over-current /
// thermal shutdown; TCA9555 internal pull-ups). The rotary switches that used these are gone.
constexpr int FLT_WH = 8, FLT_IR = 9, FLT_OTH = 10, FLT_M1 = 11;     // P10..P13
constexpr int FLT_M2 = 12, FLT_M3 = 13, FLT_RC = 14, P17_SPARE = 15;  // P14..P17
}  // namespace exp

// PCA9685 (U20) channels, push-pull (MODE2.OUTDRV = 1). Output switches are SY6288 (EN high = on, 100k
// pull-down: off at power-up, when U20 is unpowered and while /OE is high).
namespace pwm {
constexpr int RC_PWR = 15;                                         // servo 5 V switch (Q2), high = on
constexpr int RC_PAN = 1, RC_TILT = 2, RC_ROT = 4, RC_OTHER = 5;  // servo signals, 4.7k pull-ups
constexpr int LED_WHITE = 11, LED_IR = 14, LED_OTHER = 12;          // lamp switches Q3 Q4 Q5, high = on
constexpr int MISC1 = 8, MISC2 = 9, MISC3 = 10;                    // MISC.OUT switches Q6-Q8 (laser on one of these)
constexpr int EXP11 = 7, EXP12 = 6, EXP13 = 13, EXP14 = 3, EXP15 = 0;  // spare outputs on the expansion header
}  // namespace pwm

}  // namespace pins
